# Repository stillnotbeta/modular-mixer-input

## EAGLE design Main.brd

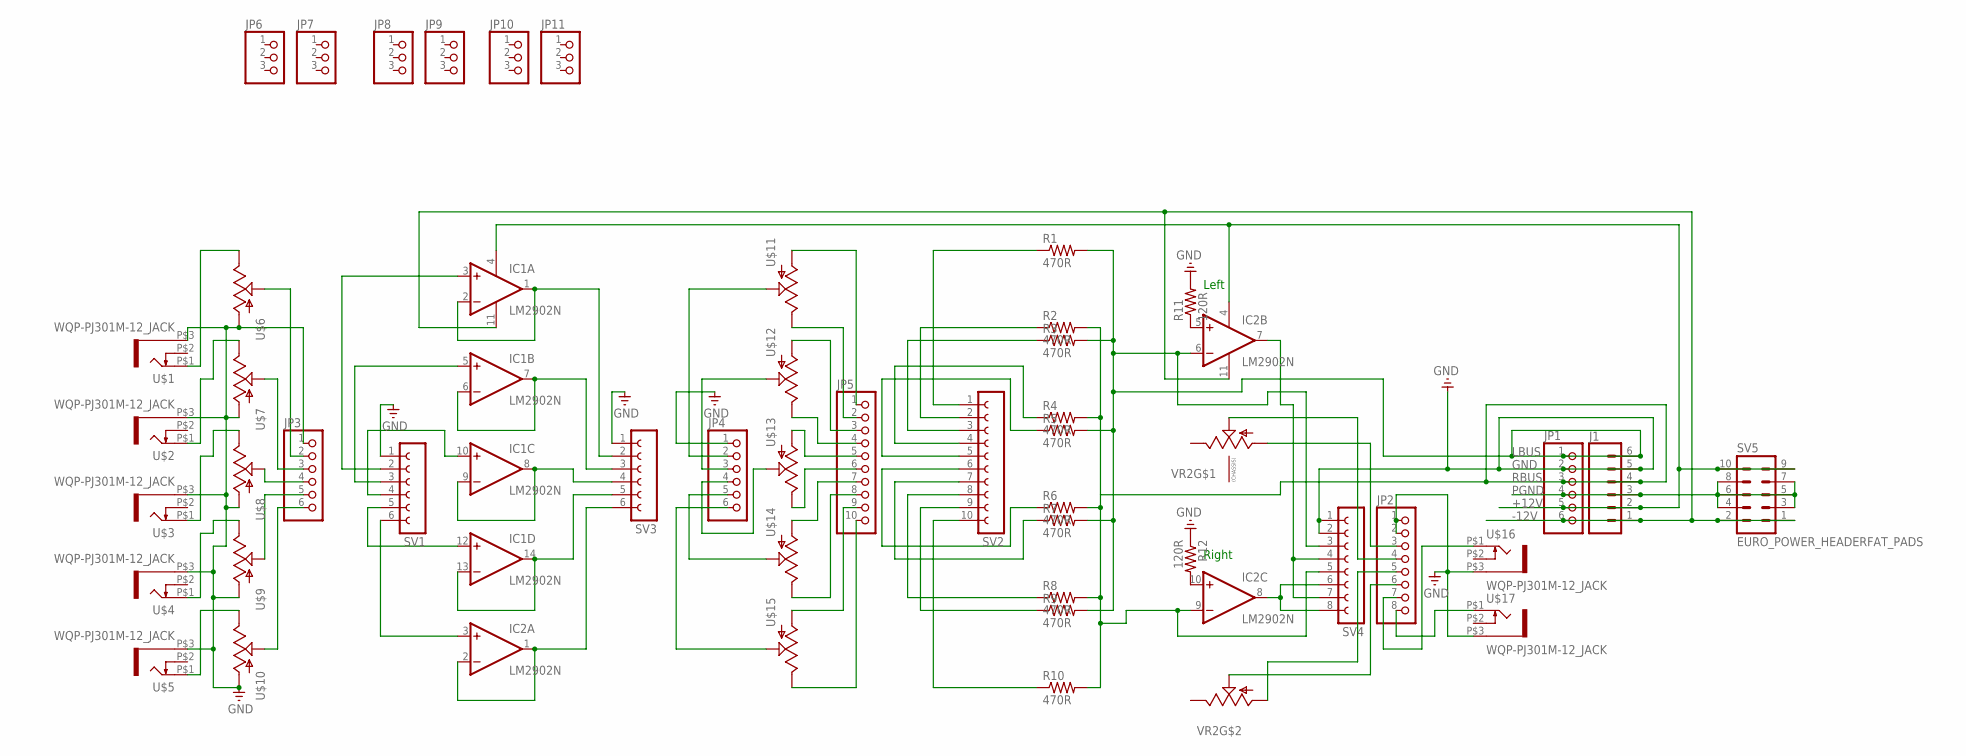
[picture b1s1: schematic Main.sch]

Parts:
IC1, IC2: LM2902N; DIL14
J1: CONN_06SMD-FEMALE-V2; 1X06-SMD-FEMALE
JP1: PINHD-1X6/90; 1X06/90
JP2: PINHD-1X8; 1X08
JP3, JP4: PINHD-1X6; 1X06
JP5: PINHD-1X10; 1X10
JP6, JP7, JP8, JP9, JP10, JP11: PINHD-1X3; 1X03
R1, R2, R3, R4, R5, R6, R7, R8, R9, R10: 470R; 0207/9
R11, R12: 120R; 0207/9
SV1, SV3: FE06-1; FE06
SV2: FE10-1; FE10
SV4: FE08-1; FE08
SV5: EURO_POWER_HEADERFAT_PADS; EURO_PWR_HEADER_FAT
U$1, U$2, U$3, U$4, U$5, U$16, U$17: WQP-PJ301M-12_JACK
U$6, U$7, U$8, U$9, U$10, U$11, U$12, U$13, U$14, U$15: POT; ALPS_POT
VR2: ALPHA-9MM-DUALPOT; DUAL_9MM_SNAP-IN_POT

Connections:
+12V: IC1.4 (V+), IC2.4 (V+), J1.2, JP1.5, SV5.9, SV5.10
-12V: IC1.11 (V-), IC2.11 (V-), J1.1, JP1.6, SV5.1, SV5.2
GND: J1.5, JP1.2, JP2.1, JP2.2, JP3.1, R11.2, R12.1, SV1.1, SV3.1, SV4.1, SV4.2, U$1.P$3 (1), U$2.P$3 (1), U$3.P$3 (1), U$4.P$3 (1), U$5.P$3 (1), U$6.P$3 (A), U$7.P$3 (A), U$8.P$3 (A), U$9.P$3 (A), U$10.P$3 (A), U$16.P$3 (1), U$17.P$3 (1)
LBUS: IC2.6 (-IN), J1.6, JP1.1, R1.2, R3.2, R5.2, R7.2, R9.2, SV4.3
unnamed: U$1.P$1 (2), U$6.P$1 (E)
unnamed: U$2.P$1 (2), U$7.P$1 (E)
unnamed: U$3.P$1 (2), U$8.P$1 (E)
unnamed: U$4.P$1 (2), U$9.P$1 (E)
unnamed: U$5.P$1 (2), U$10.P$1 (E)
unnamed: JP3.2, U$6.P$2 (S)
unnamed: JP3.3, U$7.P$2 (S)
unnamed: JP3.4, U$8.P$2 (S)
unnamed: JP3.5, U$9.P$2 (S)
unnamed: JP3.6, U$10.P$2 (S)
unnamed: IC1.1 (OUT), IC1.2 (-IN), SV3.2
unnamed: IC1.6 (-IN), IC1.7 (OUT), SV3.3
unnamed: IC1.8 (OUT), IC1.9 (-IN), SV3.4
unnamed: IC1.13 (-IN), IC1.14 (OUT), SV3.5
unnamed: IC2.1 (OUT), IC2.2 (-IN), SV3.6
unnamed: JP5.1, U$11.P$3 (A)
unnamed: JP5.2, U$11.P$1 (E)
unnamed: JP5.3, U$12.P$3 (A)
unnamed: JP5.4, U$12.P$1 (E)
unnamed: JP5.5, U$13.P$3 (A)
unnamed: JP5.6, U$13.P$1 (E)
unnamed: JP5.7, U$14.P$3 (A)
unnamed: JP5.8, U$14.P$1 (E)
unnamed: JP5.9, U$15.P$3 (A)
unnamed: JP5.10, U$15.P$1 (E)
unnamed: JP2.8, U$17.P$1 (2)
unnamed: IC1.10 (+IN), SV1.4
unnamed: IC2.5 (+IN), R11.1
unnamed: IC2.10 (+IN), R12.2
unnamed: IC2.7 (OUT), SV4.4, SV4.7
unnamed: IC1.5 (+IN), SV1.3
unnamed: IC2.3 (+IN), SV1.6
unnamed: IC1.3 (+IN), SV1.2
unnamed: IC1.12 (+IN), SV1.5
unnamed: R1.1, SV2.1
unnamed: R2.1, SV2.2
unnamed: R3.1, SV2.3
unnamed: R4.1, SV2.4
unnamed: R5.1, SV2.5
unnamed: R10.1, SV2.10
unnamed: R9.1, SV2.9
unnamed: R8.1, SV2.8
unnamed: R6.1, SV2.6
unnamed: R7.1, SV2.7
unnamed: JP4.4, U$13.P$2 (S)
unnamed: JP4.5, U$14.P$2 (S)
unnamed: JP4.6, U$15.P$2 (S)
unnamed: JP4.3, U$12.P$2 (S)
unnamed: JP4.2, U$11.P$2 (S)
unnamed: JP2.6, VR2.2B (S)
unnamed: JP2.7, U$16.P$1 (2)
unnamed: JP2.5, VR2.1B (A)
unnamed: JP2.4, VR2.2 (S)
unnamed: IC2.8 (OUT), SV4.6, SV4.8
unnamed: JP2.3, VR2.1 (A)
PGND: J1.3, JP1.4, SV5.3, SV5.4, SV5.5, SV5.6, SV5.7, SV5.8
RBUS: IC2.9 (-IN), J1.4, JP1.3, R2.2, R4.2, R6.2, R8.2, R10.2, SV4.5

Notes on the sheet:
Left
Right

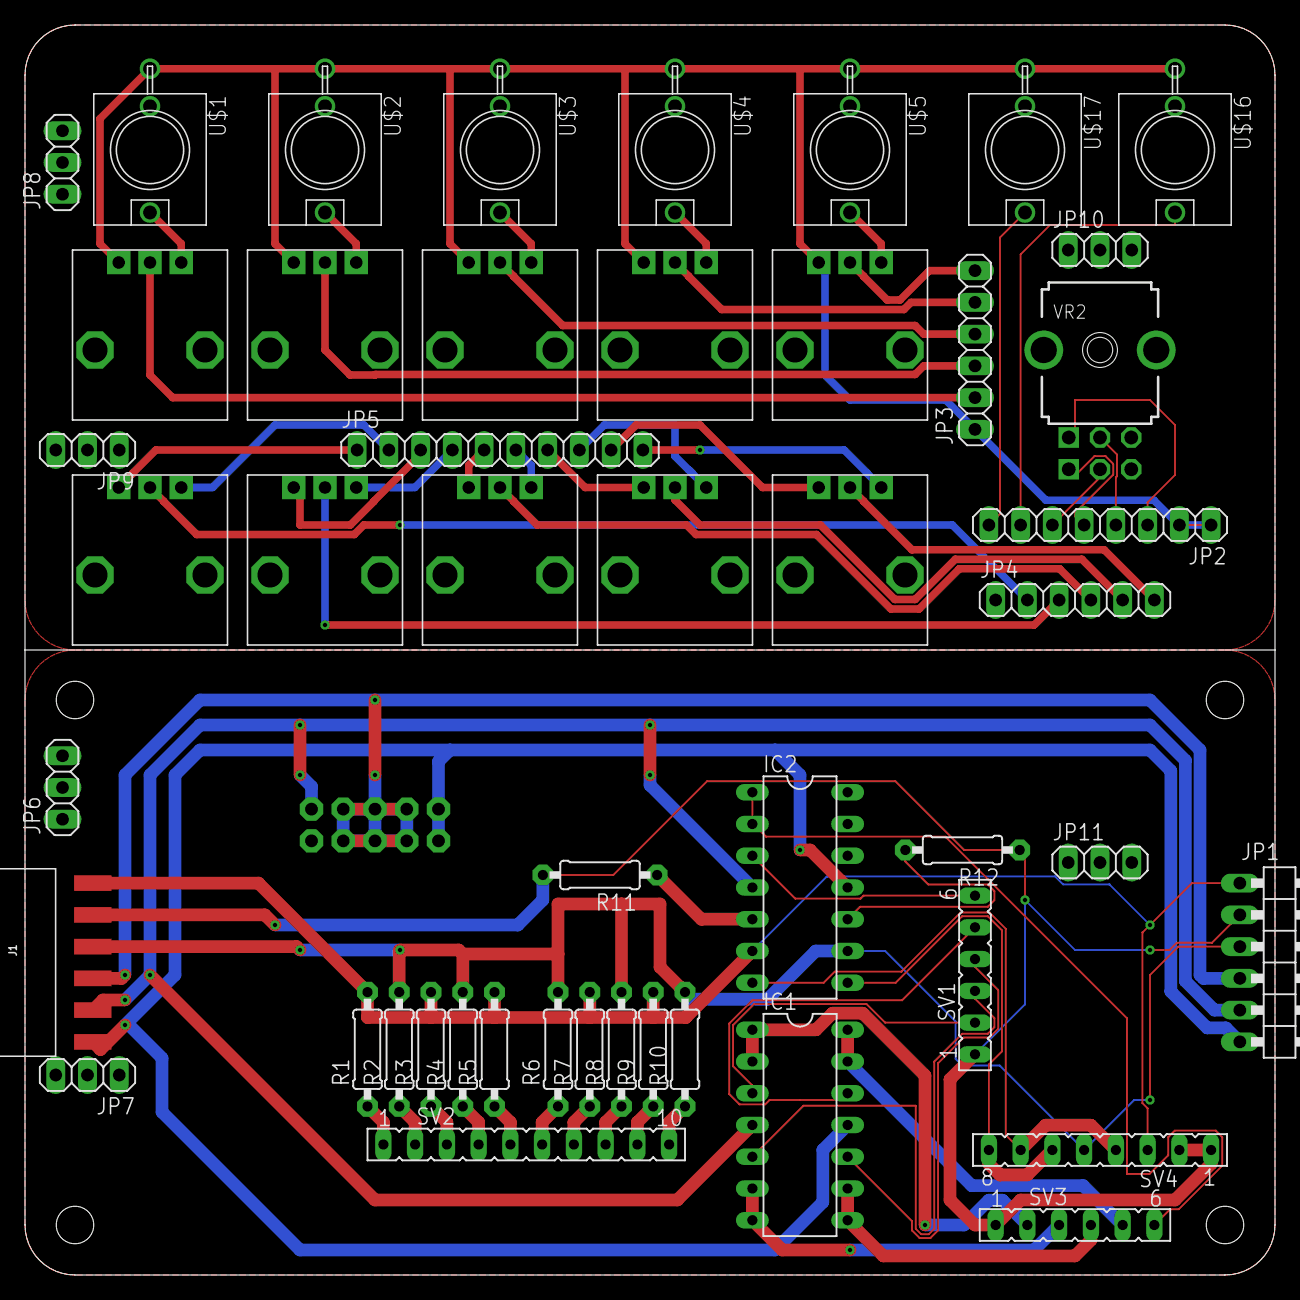
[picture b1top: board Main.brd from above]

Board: 2 copper layers, 100.0 x 100.0 mm, 49 parts (1 on the bottom side), 61 nets.

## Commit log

2019-06-12 V 1.0
    THESE FILES HAVN'T BEEN REVIEWED YET AND SHOULDN'T BE PUT INTO PRODUCTION!

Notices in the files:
parts and their libraries:
SparkFun-Connectors: Licensing: Creative Commons ShareAlike 4.0 International - https://creativecommons.org/licenses/by-sa/4.0
